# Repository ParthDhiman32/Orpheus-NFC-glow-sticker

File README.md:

So i am trying to make a NFC sticker which will be the shape of the hackclub Orpheous sticker i will make it into a pretty looking PCB which will have a NFC chip and a coil which will pick up electromagnetic waves convert them into electrical signals and then light up an LED.

# Overview
This is a Orpherous flag sticker shaped PCB which uses a NFC ICs and an energy buffering mechanism to store enough power to light up a LED
once the pcb is fabricated The original hakc club fag sticker can be sticked on top of this pcb after which the ICs and electronics won't be visible and then once we bring this near a NFC reader or any electromangentic coil which is actively pulsing energy Then this NFC's electromagnetic coil picks up that charge and then it stores all the charge inside of a energy buffer which stores enough energy to light up 3 led's and hence make the sticker glow 

# Schematics 

**The main ICs used inside this system are**
1. ST25DV04K - This is a NFC enegry harvester IC which takes the RF Signals as the input and then converts it into stable DC electic voltage
2. BD58xxE - This is a very efficient voltage detection IC which detects the flow of energy inside the circuit
3. Metic 0603 Capscitors and LEDs are used for keeping the circuit small enough to fit on a sticker

# Routing

The entire edge.cuts layes is a complx polygon which was required to be traced by hand in order to make the proper Outter PCB edge outline
The main paw had the RF antenna with 4 circualr loops each 0.25mm thick 
The main ICs is seated on the flag part
There are 3 leds 2 on the paw and one on the flag 
All are bright enough to illuminate the Sticker fully 

# 3D render 

This render appears green because it was rendered inside Kicad 
I will use a White PCB ,golden pads and Black silkscreen from JLCPCB for making this look even prettier 

# Final render

# PCB Specification

# BOM
| Designator | Component | Package | Qty | Est. Unit Price (USD) | Total Price (USD) |
| :--- | :--- | :--- | :--- | :--- | :--- |
| **U1** | ST25DV04K (NFC Harvester IC) | SO8 | 1 | $0.90 | $0.90 |
| **U2** | BD48K23G (2.3V Voltage Supervisor) | SOT-23-3 | 1 | $0.30 | $0.30 |
| **C2** | 10 µF Capacitor | 0603 | 1 | $0.02 | $0.02 |
| **C3** | 100 nF Capacitor | 0603 | 1 | $0.01 | $0.01 |
| **R1, R2, R3** | 330 Ω Resistor | 0603 | 3 | $0.01 | $0.03 |
| **D1, D2, D3** | LED (Any Color) | 0603 | 3 | $0.03 | $0.09 |

**Total Component Cost:** ~$1.35 per board<br>
**PCB Cost - 2.1$** <br>
**Total Estimated Cost (PCB + Components): ~$3.45 per unit**<br>

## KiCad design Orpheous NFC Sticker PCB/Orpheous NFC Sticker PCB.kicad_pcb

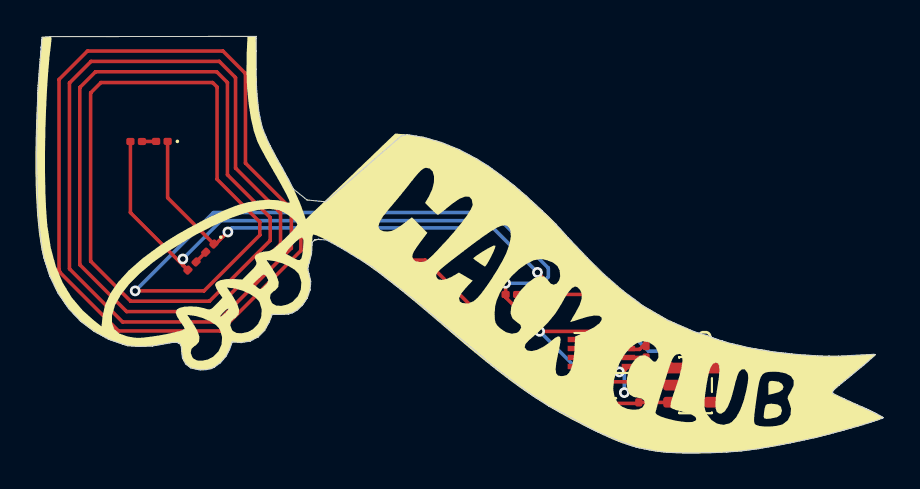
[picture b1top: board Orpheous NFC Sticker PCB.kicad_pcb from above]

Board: 2 copper layers, 47.0 x 23.1 mm, 11 parts (0 on the bottom side), 7 nets.

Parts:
C1: 10pF; C_0201_0603Metric
C2: 10uF; C_0201_0603Metric
C3: 100nF; C_0201_0603Metric
D1, D2, D3: LED; LED_0201_0603Metric
R1, R2, R3: 330; R_0201_0603Metric
U1: ST25DV04K; DFN-8-1EP_3x2mm_P0.5mm_EP1.36x1.46mm
U2: BD48ExxG; SOT-23-5

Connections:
/ANT1: C1.1, C1.2, U1.2 (AC0)
GND: C2.1, C3.1, R1.2, R2.2, R3.2, U1.4 (VSS), U2.3 (GND)
unnamed: D1.2 (A), R1.1
unnamed: D1.1 (K), D2.1 (K), D3.1 (K), U2.1 (VOUT)
unnamed: D2.2 (A), R2.1
unnamed: D3.2 (A), R3.1
unnamed: C2.2, C3.2, U1.1 (V_EH), U2.2 (VDD)

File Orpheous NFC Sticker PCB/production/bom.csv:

Designator,Footprint,Quantity,Value,LCSC Part #
C1,0201,1,10pF,
C2,0201,1,10uF,
C3,0201,1,100nF,
"D1, D2, D3",0201,3,LED,
"R1, R2, R3",0201,3,330,
U1,DFN-8-1EP_3x2mm_P0.5mm_EP1.36x1.46mm,1,ST25DV04K,
U2,SOT-23-5,1,BD48ExxG,
